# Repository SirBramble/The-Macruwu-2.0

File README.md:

# The Macruwu
The macro pad for all! (well, at least, if you can understand the Clusterfuck posted here)
The Firmware is based on the Arduino Pico Core by earlephilhower https://github.com/earlephilhower/arduino-pico. 

**This is only a brief overview** The full documentation and instructions can be found in the "Documentation"-folder.

## Components used

I went with the RP2040 based board from seeed studio. It has a fast chip, offers integrated USB support and is only about 6€. However, it has limited GPIO pins. So if you want to build your own, I would recommend using I/O Expanders or something similar. Another option would be to use a raspberry Pi with a RP2040. This Board beaks out most of the RP2040 Pins and has Options for Wi-Fi.

In order to try out different Key switches and keep the Macruwu modular, I decided to use hot swap sockets. They aren’t to expensive, if you order them for AliExpress (about 1\$/10psc). But beware, when soldering. If your board manufacturer decides to give you the shit coating on your Pads, prepare for heavy flux use.

For the I/O Expanders I used the PCA9555 from NXP. They conveniently don’t need a lot of setup and are automatically set to INPUT_PULLUP. The detailed Addressing scheme and co can be found in the Datasheet. But, as per usual nowadays, the I/O expanders are sold out. So, you might want to look for them somewhere else, or find a suitable replacement. But if you can find them, I can recommend the NXP Expanders. They need minimal to no Software Setup and I haven't had a dead one so far.

The level shifter (TXU0104PWR) is a cheap option I got from Mouser. It has 4 channels it can shift and is enough for the two 5V I²C Lines and the neopixel line.

The keyswitches were purchased for AliExpress and some smaller Keyboard parts suppliers. I like clicky switches, so I went for the Gateron greens. However, I cannot recommend them. They sound quite hollow and scratchy. Could maybe fixed with some lube *gigidy*, but it’s not really worth the trouble. 
If you want some really clicky Keyswitches, that will any the hell out of anybody in a 30km Radius, you could go for the Kailh Low profile Chock whites. My, extremely pissed of, fellow student can confirm. However, be aware that they can not be used with relegendable keycaps.
## How to compile

### With the Arduino IDE 2.0
#### Macruwu
First download the Code either from the repo or via the release tab. Put it in a folder and open the ```Macruwu_OS.ino``` file.

In order to compile the Code, you need to install the Arduino Pico core. There is a Tutorial on how to do this on earlephilhowers GitHub. You will also need the Adafruit SPIFlash Library. It can be downloaded via the Library Manager. The rest should be included in the Pico Core.
If you get Library conflicts, I'm afraid you're on you’re own. I somehow got it to compile and haven’t touched my setup since. No Idea why it suddenly worked, but the only thing I can recommend, is to back up your libraries and start fresh.

EDIT: If you get a Library conflict, you may want to look for other Bugs. Sometimes the Arduino IDE shows this message, just to inform you, that it has used a certain Library. However, your Code may not compile due to another error.

Also remember to change the USB Stack to the Adafruit TinyUsb Stack via Tools->USB Stack.
If you want to use the inbuilt Flash as a drive, you also have to allocate Memory under Tools->Flash Size. The first time you allocate Memory, you will have to format it. Just doing it in Windows should be fine.
P.s. The flash drive code is more or less copied from Adafruit. sorry, I was lazy...

#### Bluetuwu
First download the Code either from the repo or via the release tab. Put it in a folder and open the ```Bluetuwu_OS.ino``` file.

To Compile the Code you need to install the ESP32 Arduino Core from Espressif. After you installed this, you can just upload with the standard Settings.

### With PlatformIO
Well... I have no Idea, but let me know, if you find out.

## How to use (isch...)

The Macruwu OS is divided in to several Files for maximum ```'someFuckingShit' is not defined did you mean 'goFuckYourself'?```

### With macroLayout.txt

NOTE: The first time you start the Macruwu, you might have problem, with it crashing. This may be caused by the File not being present in the Flash directory. You may have to disable the ```readFile```-function in the ```Keyboard::init```-function in ```Keyboard.cpp``` and upload the File first. Then reenable the function and it should run.

The Layout can be set with several Commands. ```Layer x: ``` sets the Layer under which the Buttons will be accessible. ```Button x: {string}``` sets the Button and is followed by the string, that will be printed by the keyboard. Remember to leave a space between ```:``` and ```{string}```. This is due to the way that the file gets read. The Character straight after the ```:``` will be ignored.

So far, most characters will be interpreted correctly, however ```<``` and ```>``` have a special Meaning. They press the left and right arrow keys respectively. Verry useful for Macro pads that print code with a lot of Brackets. Other functions have not yet been implemented, but feel free to add them in the ```Keyboard.cpp``` under ```Keyboard::interpet```.

In order to read the file from the Flash in to the Data structure you want to run the ```readFile```-function at least once. I recommend running it once in ```setup()``` and then running it each time the file is changed. this can be done with:
```
if(Macruwu.fsChanged()){
    Macruwu.readFile();
  }
```

In order to run the commands that have been set in the Data structure you will have to run the ```interpret(layer, button)```-function.

### With Hardcoded Mapping
The Keymapping can be set in the ```Mapping.cpp```.

In order to write something over USB, you can use ```Keyboard1.write("something");``` But this only works for most normal characters like letters and sometimes other specialty symbols. You'll have to try it out. Things like Brackets or things that use function keys, will have to be set up manually. This can either be done, by sending the commands via the Tiny USB library directly, or by adding a new function to the Keyboard class. But look through the Keyboard class, as I may add more functions in the future.

**Word of Warning:** If you do not have a US Keyboard, be prepared for some HID Code treasure hunting. I haven’t found a way to change the layout, so you either have to find a Layout and redefine all the keys in the library, or just try and hope you find what you need. If you have a German Keyboard layout set, you can reference the code for some mappings.

## Bugs
Yes

## Further documentation
I recommend reading the documentation by earlephilhower https://github.com/earlephilhower/arduino-pico. It´s a far better than this clusterfuck, but feel free to look through the code.

And in case you didn't read the first 3 lines, you can find more documentation in the "Documentation"-folder.

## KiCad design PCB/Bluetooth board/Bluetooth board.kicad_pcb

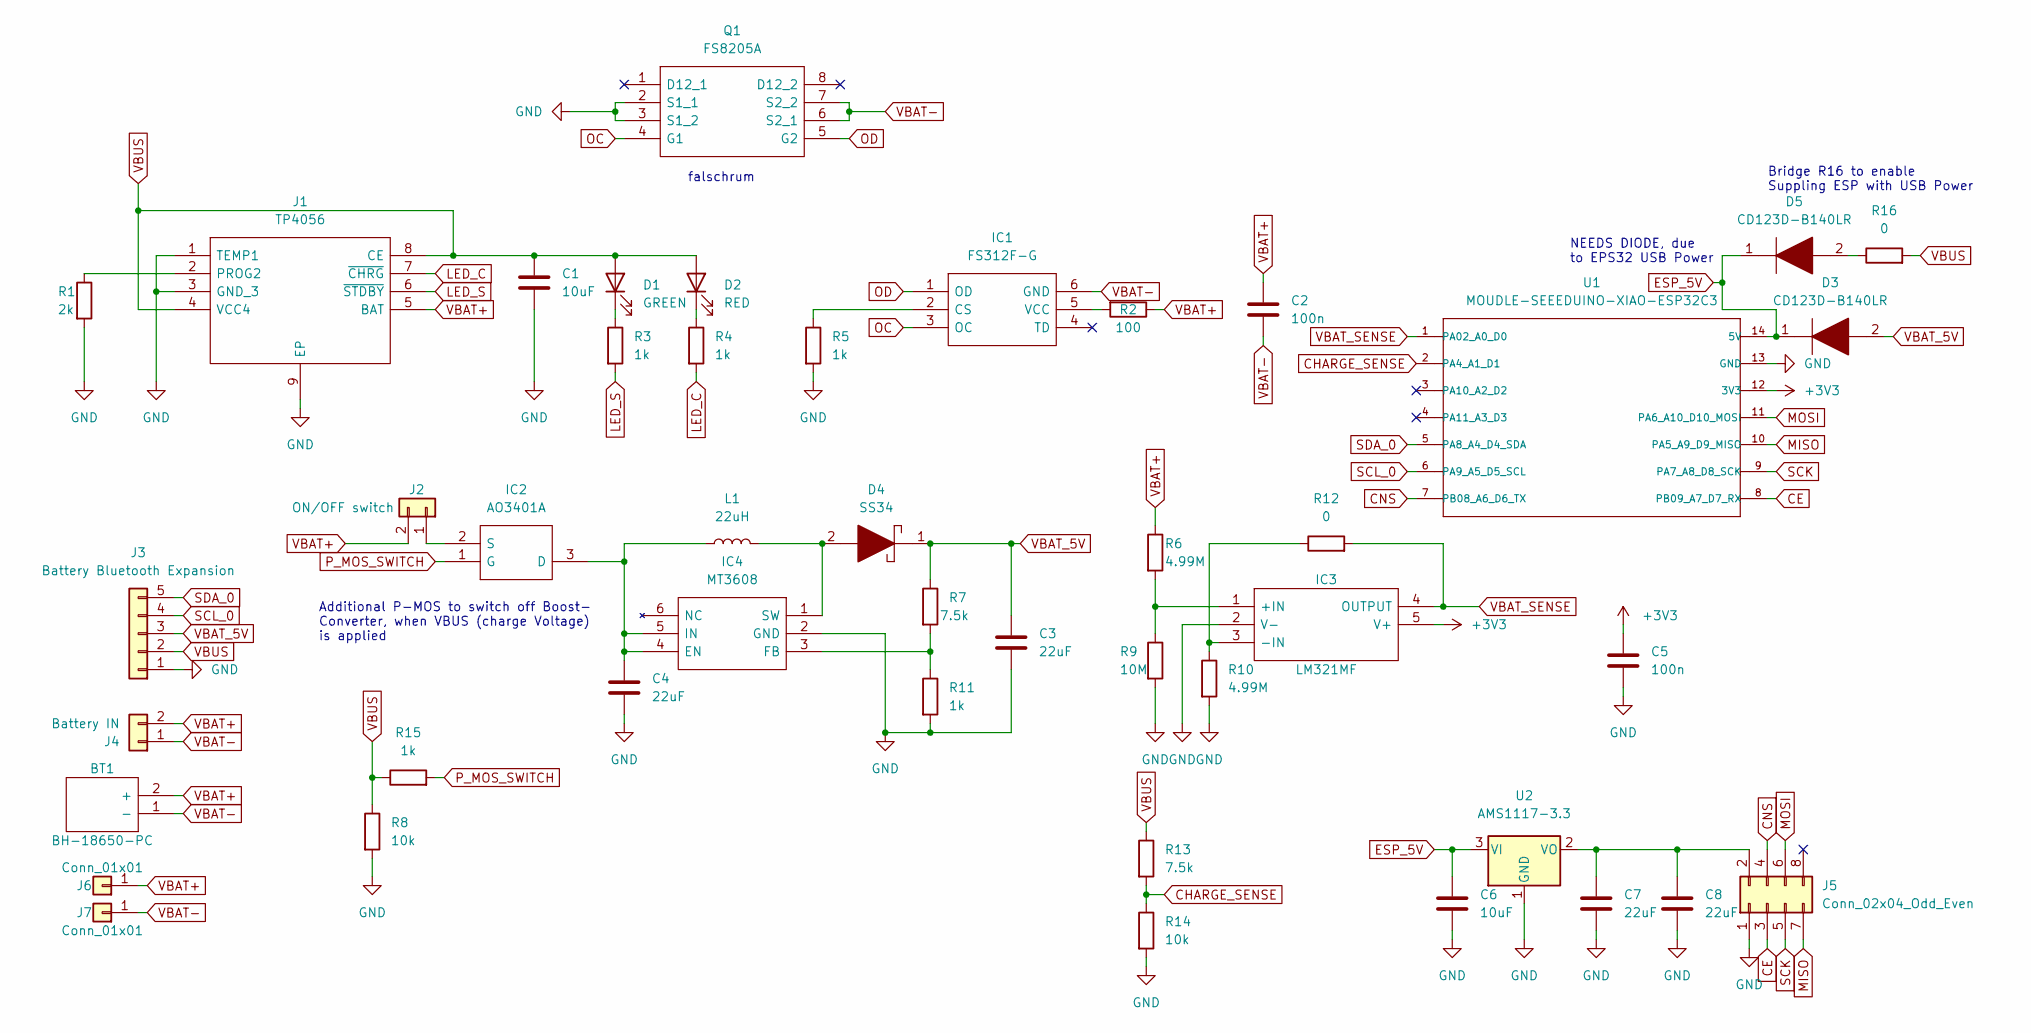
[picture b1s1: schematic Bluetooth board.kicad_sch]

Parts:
BT1: BH-18650-PC; BH18650PC; Manufacturer_Part_Number BH-18650-PC
C1, C6: 10uF; C_0603_1608Metric_Pad1.08x0.95mm_HandSolder; LCSC Part # C96446
C2, C5: 100n; C_0603_1608Metric_Pad1.08x0.95mm_HandSolder; LCSC Part # C14663
C3, C4, C7, C8: 22uF; C_1206_3216Metric_Pad1.33x1.80mm_HandSolder; LCSC Part # C12891
D1: GREEN; LED_D5.0mm
D2: RED; LED_D5.0mm
D3, D5: CD123D-B140LR; CD123DB140LR; Manufacturer_Part_Number CD123D-B140LR; Mouser Part Number 652-CD123D-B140LR
D4: SS34; D_SMA; Manufacturer_Part_Number SS34; Mouser Part Number 821-SS34
IC1: FS312F-G; SOT95P280X145-6N; Manufacturer_Part_Number FS312F-G; LCSC Part # C82736
IC2: AO3401A; SOT95P237X112-3N; Manufacturer_Part_Number IRLML6401; LCSC Part # C15127
IC3: LM321MF; SOT95P280X145-5N; Manufacturer_Part_Number LM321MF; Mouser Part Number 926-LM321MF
IC4: MT3608; SOT95P280X145-6N; Manufacturer_Part_Number MT3608; LCSC Part # C84817
J1: TP4056; SOIC127P600X175-9N; Manufacturer_Part_Number TP4056; LCSC Part # C16581
J2: ON/OFF switch; PinHeader_1x02_P2.54mm_Vertical
J3: Battery Bluetooth Expansion; PinSocket_1x05_P2.54mm_Vertical
J4: Battery IN; PinHeader_1x02_P2.54mm_Vertical
J5: Conn_02x04_Odd_Even; PinHeader_2x04_P2.54mm_Vertical
J6, J7: Conn_01x01; A FUCKING PAD
L1: 22uH; L_12x12mm_H6mm; LCSC Part # C2929501
Q1: FS8205A; SOP65P640X120-8N; Manufacturer_Part_Number FS8205A; LCSC Part # C16052
R1: 2k; R_0603_1608Metric_Pad0.98x0.95mm_HandSolder; LCSC Part # C22975
R2: 100; R_0603_1608Metric_Pad0.98x0.95mm_HandSolder; LCSC Part # C22775
R3, R4, R5, R11, R15: 1k; R_0603_1608Metric_Pad0.98x0.95mm_HandSolder; LCSC Part # C21190
R6, R10: 4.99M; R_0603_1608Metric_Pad0.98x0.95mm_HandSolder; LCSC Part # C158914
R7, R13: 7.5k; R_0603_1608Metric_Pad0.98x0.95mm_HandSolder; LCSC Part # C5140717
R8, R14: 10k; R_0603_1608Metric_Pad0.98x0.95mm_HandSolder; LCSC Part # C25804
R9: 10M; R_0603_1608Metric_Pad0.98x0.95mm_HandSolder; LCSC Part # C2907090
R12, R16: 0; R_0603_1608Metric_Pad0.98x0.95mm_HandSolder
U1: MOUDLE-SEEEDUINO-XIAO-ESP32C3; MOUDLE14P-SMD-2.54-21X17.8MM
U2: AMS1117-3.3; SOT-223-3_TabPin2; LCSC Part # C6186

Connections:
+3V3: C5.1, IC3.5 (V+), U1.12 (3V3)
CE: J5.3, U1.8 (PB09_A7_D7_RX)
CHARGE_SENSE: R13.2, R14.1, U1.2 (PA4_A1_D1)
CNS: J5.4, U1.7 (PB08_A6_D6_TX)
ESP_5V: C6.1, D3.1, D5.1, U1.14 (5V), U2.3 (VI)
GND: C1.2, C3.2, C4.2, C5.2, C6.2, C7.2, C8.2, IC3.2 (V-), IC4.2 (GND), J1.1 (TEMP1), J1.3 (GND_3), J1.9 (EP), J3.1, J5.1, Q1.2 (S1_1), Q1.3 (S1_2), R1.2, R5.2, R8.2, R9.2, R10.2, R11.2, R14.2, U1.13 (GND), U2.1 (GND)
LED_C: J1.7 (~CHRG), R4.2
LED_S: J1.6 (~STDBY), R3.2
MISO: J5.7, U1.10 (PA5_A9_D9_MISO)
MOSI: J5.6, U1.11 (PA6_A10_D10_MOSI)
unnamed: C4.1, IC2.3 (D), IC4.4 (EN), IC4.5 (IN), L1.1
unnamed: C7.1, C8.1, J5.2, U2.2 (VO)
unnamed: D1.1 (K), R3.1
unnamed: D2.1 (K), R4.1
unnamed: D4.2, IC4.1 (SW), L1.2
unnamed: D5.2, R16.1
unnamed: IC1.2 (CS), R5.1
unnamed: IC1.5 (VCC), R2.2
unnamed: IC2.2 (S), J2.1
unnamed: IC3.1 (+IN), R6.2, R9.1
unnamed: IC3.3 (-IN), R10.1, R12.1
unnamed: IC4.3 (FB), R7.2, R11.1
unnamed: J1.2 (PROG2), R1.1
OC: IC1.3 (OC), Q1.4 (G1)
OD: IC1.1 (OD), Q1.5 (G2)
P_MOS_SWITCH: IC2.1 (G), R15.2
SCK: J5.5, U1.9 (PA7_A8_D8_SCK)
SCL_0: J3.4, U1.6 (PA9_A5_D5_SCL)
SDA_0: J3.5, U1.5 (PA8_A4_D4_SDA)
VBAT+: BT1.2 (+), C2.1, J1.5 (BAT), J2.2, J4.2, J6.1, R2.1, R6.1
VBAT-: BT1.1 (-), C2.2, IC1.6 (GND), J4.1, J7.1, Q1.6 (S2_1), Q1.7 (S2_2)
VBAT_5V: C3.1, D3.2, D4.1, J3.3, R7.1
VBAT_SENSE: IC3.4 (OUTPUT), R12.2, U1.1 (PA02_A0_D0)
VBUS: C1.1, D1.2 (A), D2.2 (A), J1.4 (VCC4), J1.8 (CE), J3.2, R8.1, R13.1, R15.1, R16.2

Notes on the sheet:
falschrum
Bridge R16 to enable Suppling ESP with USB Power
NEEDS DIODE, due to EPS32 USB Power
Additional P-MOS to switch off Boost- Converter, when VBUS (charge Voltage) is applied

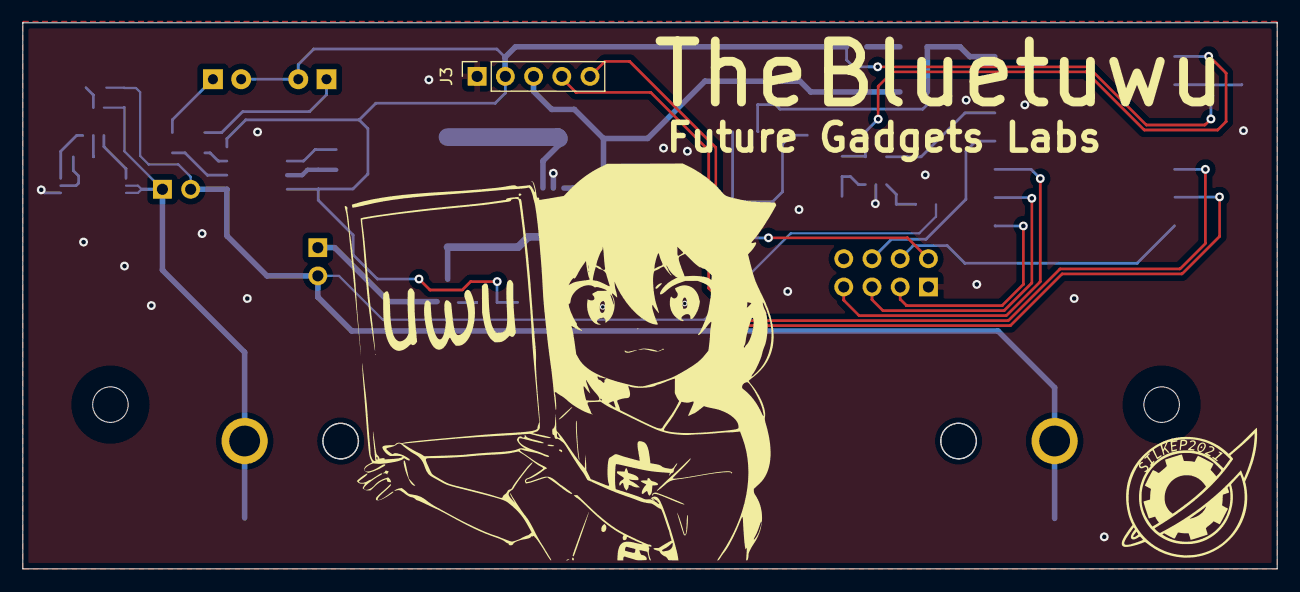
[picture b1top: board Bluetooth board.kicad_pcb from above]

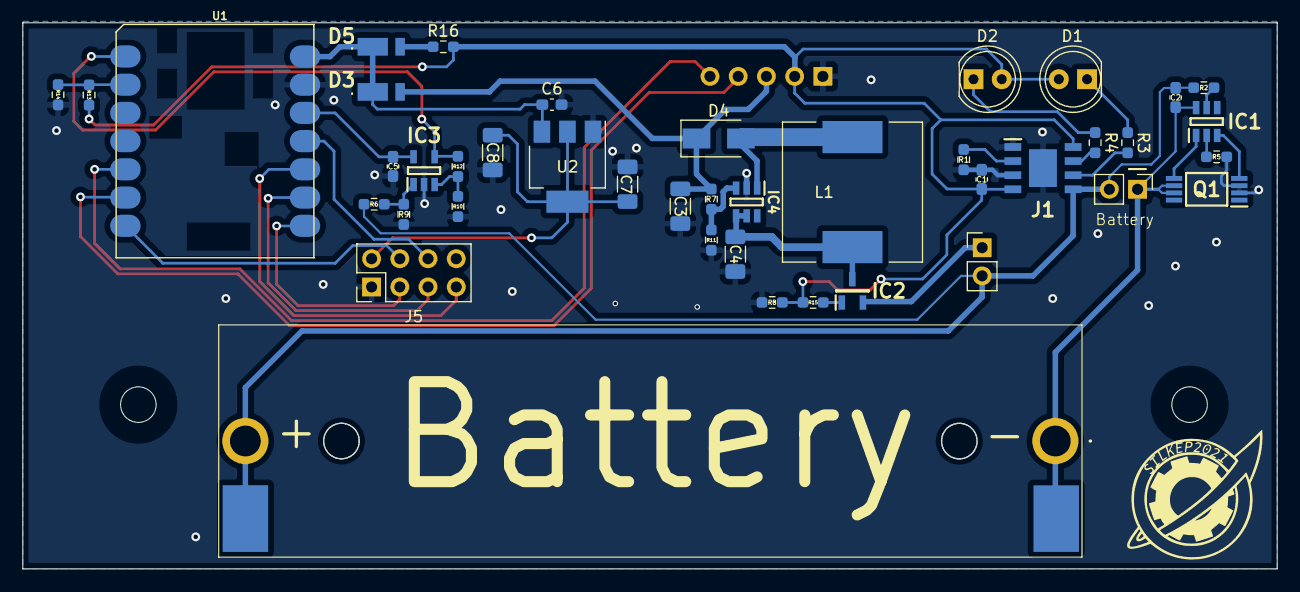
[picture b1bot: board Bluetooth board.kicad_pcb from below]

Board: 2 copper layers, 112.9 x 49.1 mm, 45 parts (44 on the bottom side), 34 nets.

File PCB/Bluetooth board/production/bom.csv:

Designator,Footprint,Quantity,Value,LCSC Part #
C1,0603,1,10uF,C96446
C2,0603,1,100n,C14663
C3,1206,1,22uF,C12891
C4,1206,1,22uF,C12891
C5,0603,1,100n,C14663
C6,0603,1,10uF,C96446
C7,1206,1,22uF,C12891
C8,1206,1,22uF,C12891
D4,D_SMA,1,SS34,C8678
IC1,SOT95P280X145-6N,1,FS312F-G,C82736
IC2,SOT95P237X112-3N,1,AO3401A,C15127
IC3,SOT95P280X145-5N,1,LM321MF,C668208
IC4,SOT95P280X145-6N,1,MT3608,C84817
J1,SOIC127P600X175-9N,1,TP4056,C16581
L1,L_12x12mm_H6mm,1,22uH,C2929501
Q1,SOP65P640X120-8N,1,FS8205A,C16052
R1,0603,1,2k,C22975
R10,0603,1,4.99M,C158914
R11,0603,1,1k,C21190
R13,0603,1,7.5k,C5140717
R14,0603,1,10k,C25804
R15,0603,1,1k,C21190
R2,0603,1,100,C22775
R3,0603,1,1k,C21190
R4,0603,1,1k,C21190
R5,0603,1,1k,C21190
R6,0603,1,4.99M,C158914
R7,0603,1, 7.5k,C5140717
R8,0603,1,10k,C25804
R9,0603,1,10M,C2907090
U2,SOT-223-3_TabPin2,1,AMS1117-3.3,C6186

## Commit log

2023-03-11 updated macroLayout.txt
2023-08-30 updated firmware
2024-02-04 ported firmware from Typeuwu. (it's a lot better now...)
2024-05-08 fixed buig with I2C
2024-10-25 added new layout.txt
